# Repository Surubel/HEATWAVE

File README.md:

View this project on [CADLAB.io](https://cadlab.io/project/23592). 

# HEATWAVE
An experiment into flight controllers for racing drones.

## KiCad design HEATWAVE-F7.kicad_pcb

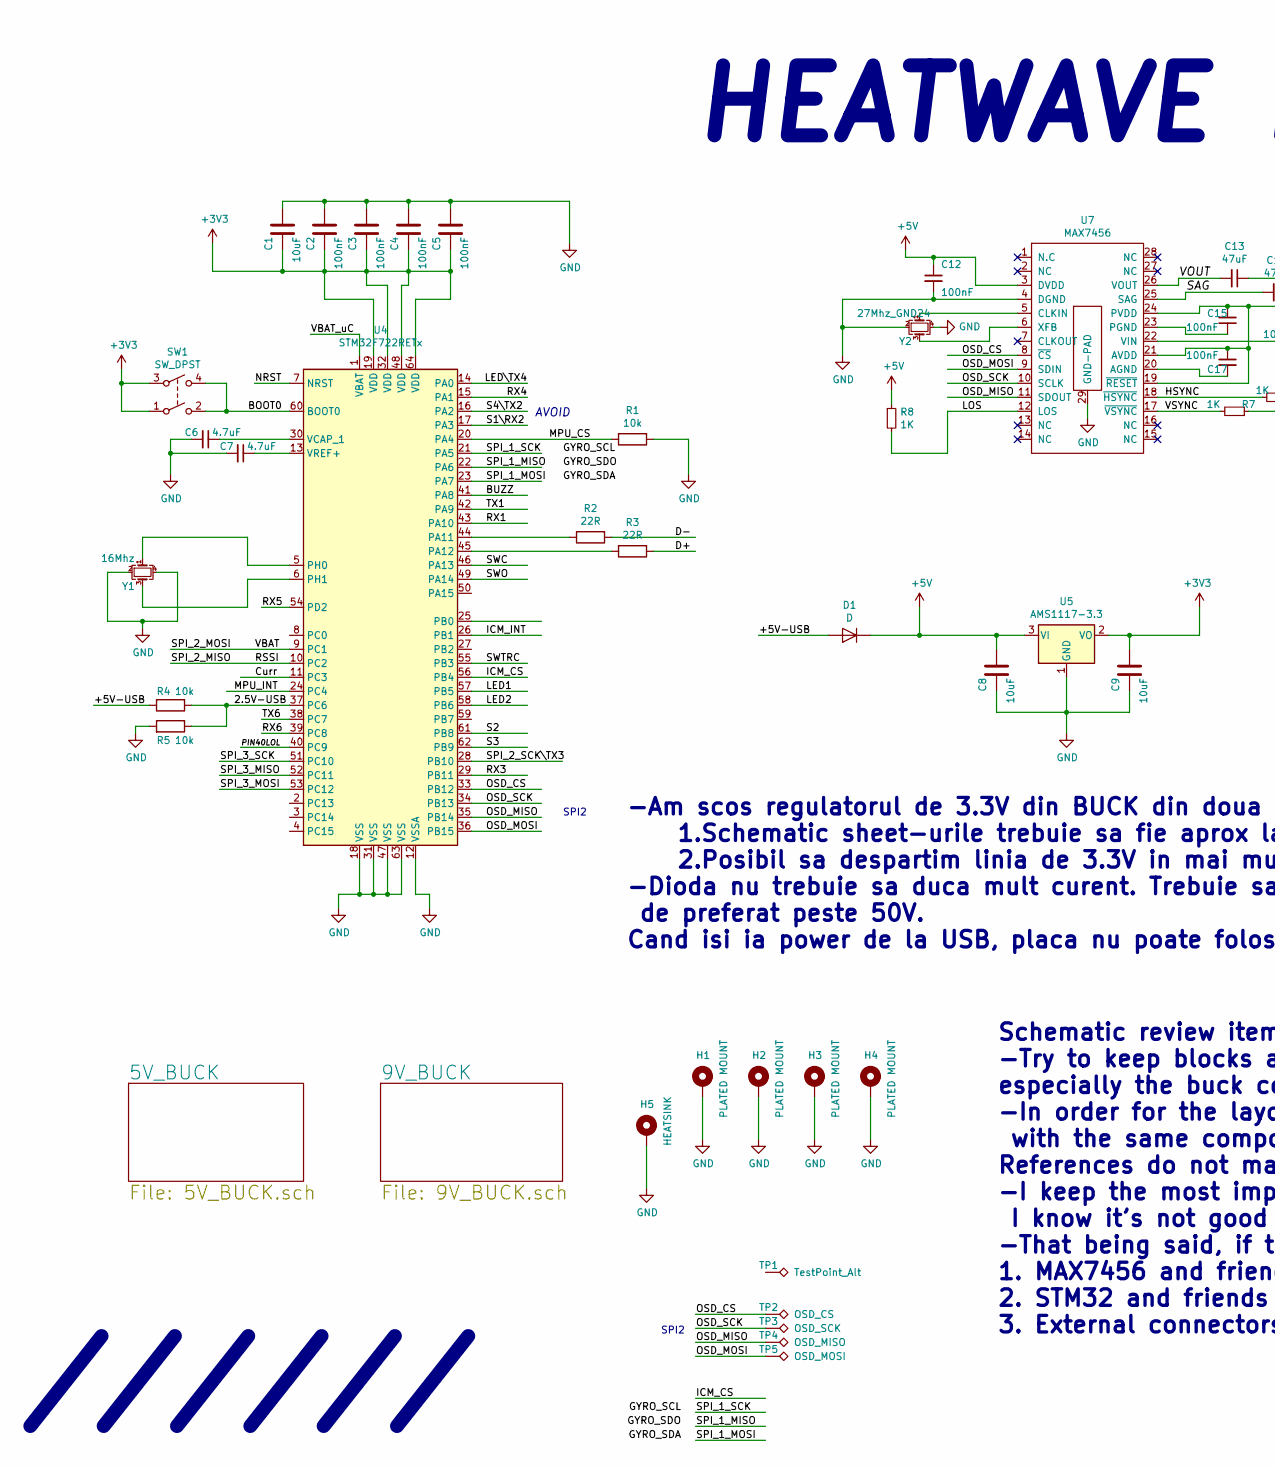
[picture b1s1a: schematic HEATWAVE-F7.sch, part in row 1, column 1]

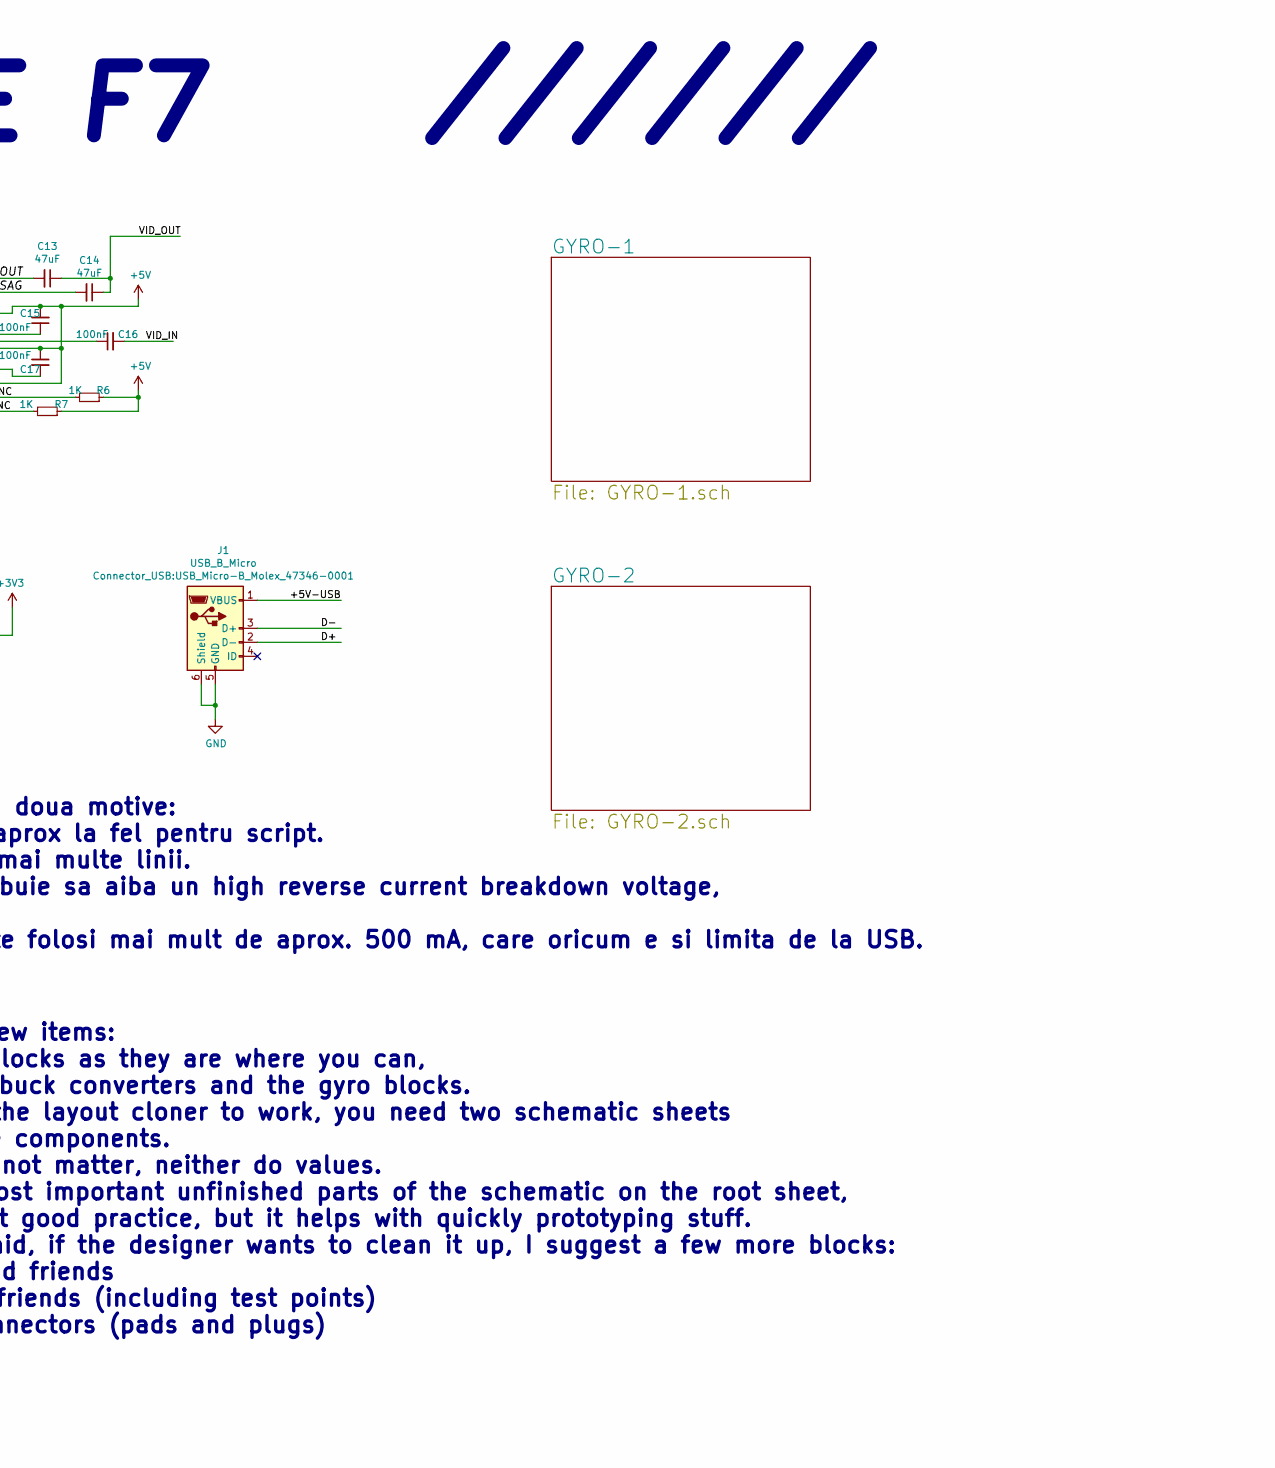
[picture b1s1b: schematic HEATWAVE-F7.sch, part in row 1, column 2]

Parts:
C1, C8, C9: 10uF; C_0805_2012Metric
C2, C3, C4, C5, C12, C15, C16, C17: 100nF; C_0805_2012Metric
C6, C7: 4.7uF; C_0402_1005Metric
C13, C14: 47uF; C_1210_3225Metric
D1: D; D_0805_2012Metric
H1, H2, H3, H4: PLATED MOUNT; MountingHole_4.5mm_Pad_Via
H5: HEATSINK; Heatsink_Aavid-TV5G_TO220_Horizontal
J1: USB_B_Micro; USB_Micro-B_Molex_47346-0001
R1, R4, R5: 10k; R_0402_1005Metric
R2, R3: 22R; R_0402_1005Metric
R6, R7, R8: 1K; R_0402_1005Metric
SW1: SW_DPST; SW_SPST_SKQG_WithoutStem
TP1: TestPoint_Alt
TP2: OSD_CS
TP3: OSD_SCK
TP4: OSD_MISO
TP5: OSD_MOSI
U4: STM32F722RETx; LQFP-64_10x10mm_P0.5mm
U5: AMS1117-3.3; SOT-223-3_TabPin2
U7: MAX7456; TSSOP-28-1EP_4.4x9.7mm_P0.65mm
Y1: 16Mhz; Resonator_SMD_muRata_CSTxExxV-3Pin_3.0x1.1mm
Y2: 27Mhz_GND24; Resonator_SMD_muRata_CSTxExxV-3Pin_3.0x1.1mm

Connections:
+3V3: C1.1, C2.1, C3.1, C4.1, C5.1, C9.2, SW1.1, SW1.3, U4.19 (VDD), U4.32 (VDD), U4.48 (VDD), U4.64 (VDD), U5.2 (VO); also elsewhere on the board
+5V: C8.2, C12.1, C15.2, C17.1, D1.1 (K), R6.1, R7.1, R8.1, U5.3 (VI), U7.3 (DVDD), U7.19 (~RESET), U7.21 (AVDD), U7.24 (PVDD); also elsewhere on the board
/2.5V-USB: R4.1, R5.1, U4.37 (PC6)
/+5V-USB: D1.2 (A), J1.1 (VBUS), R4.2
/BOOT0: SW1.2, SW1.4, U4.60 (BOOT0)
/BUZZ: U4.41 (PA8)
/Curr: U4.11 (PC3)
/D+: J1.2 (D-), R3.1
/D-: J1.3 (D+), R2.1
/HSYNC: R6.2, U7.18 (~HSYNC)
/ICM_CS: U4.56 (PB4)
/ICM_INT: U4.26 (PB1)
/LED1: U4.57 (PB5)
/LED2: U4.58 (PB6)
/LED\TX4: U4.14 (PA0)
/LOS: R8.2, U7.12 (LOS)
/MPU_CS: R1.2, U4.20 (PA4)
/MPU_INT: U4.24 (PC4)
/NRST: U4.7 (NRST)
/OSD_CS: TP2.1, U4.33 (PB12), U7.8 (~CS)
/OSD_MISO: TP4.1, U4.35 (PB14), U7.11 (SDOUT)
/OSD_MOSI: TP5.1, U4.36 (PB15), U7.9 (SDIN)
/OSD_SCK: TP3.1, U4.34 (PB13), U7.10 (SCLK)
/PIN40LOL: U4.40 (PC9)
/RSSI: U4.10 (PC2)
/RX1: U4.43 (PA10)
/RX3: U4.29 (PB11)
/RX4: U4.15 (PA1)
/RX5: U4.54 (PD2)
/RX6: U4.39 (PC8)
/S1\RX2: U4.17 (PA3)
/S2: U4.61 (PB8)
/S3: U4.62 (PB9)
/S4\TX2: U4.16 (PA2)
/SAG: C14.2, U7.25 (SAG)
/SPI_1_MISO: U4.22 (PA6)
/SPI_1_MOSI: U4.23 (PA7)
/SPI_1_SCK: U4.21 (PA5)
/SPI_2_MOSI: U4.9 (PC1)
/SPI_2_SCK\TX3: U4.28 (PB10)
/SPI_3_MISO: U4.52 (PC11)
/SPI_3_MOSI: U4.53 (PC12)
/SPI_3_SCK: U4.51 (PC10)
/SWC: U4.46 (PA13)
/SWO: U4.49 (PA14)
/SWTRC: U4.55 (PB3)
/TX1: U4.42 (PA9)
/TX6: U4.38 (PC7)
/VBAT_uC: U4.1 (VBAT)
/VID_IN: C16.2
/VID_OUT: C13.1, C14.1
/VOUT: C13.2, U7.26 (VOUT)
/VSYNC: R7.2, U7.17 (~VSYNC)
GND: C1.2, C2.2, C3.2, C4.2, C5.2, C6.2, C7.2, C8.1, C9.1, C12.2, H1.1, H2.1, H3.1, H4.1, H5.1, J1.5 (GND), J1.6 (Shield), R1.1, R5.2, U4.12 (VSSA), U4.18 (VSS), U4.31 (VSS), U4.47 (VSS), U4.63 (VSS), U5.1 (GND), U7.4 (DGND), U7.29 (GND-PAD), Y1.2, Y1.4, Y2.2, Y2.4; also elsewhere on the board
unnamed: C6.1, U4.30 (VCAP_1)
unnamed: C7.1, U4.13 (VREF+)
unnamed: C15.1, U7.23 (PGND)
unnamed: C16.1, U7.22 (VIN)
unnamed: C17.2, U7.20 (AGND)
unnamed: R2.2, U4.44 (PA11)
unnamed: R3.2, U4.45 (PA12)
unnamed: U4.5 (PH0), Y1.1
unnamed: U4.6 (PH1), Y1.3
unnamed: U7.5 (CLKIN), Y2.1
unnamed: U7.6 (XFB), Y2.3

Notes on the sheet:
HEATWAVE F7
//////
AVOID
SPI2
-Am scos regulatorul de 3.3V din BUCK din doua motive: 1.Schematic sheet-urile trebuie sa fie aprox la fel pentru script. 2.Posibil sa despartim linia de 3.3V in mai multe linii. -Dioda nu trebuie sa duca mult curent. Trebuie sa aiba un high reverse current breakdown voltage, de preferat peste 50V.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
Schematic review items: -Try to keep blocks as they are where you can, especially the buck converters and the gyro blocks. -In order for the layout cloner to work, you need two schematic sheets with the same components. References do not matter, neither do values. -I keep the most important unfinis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

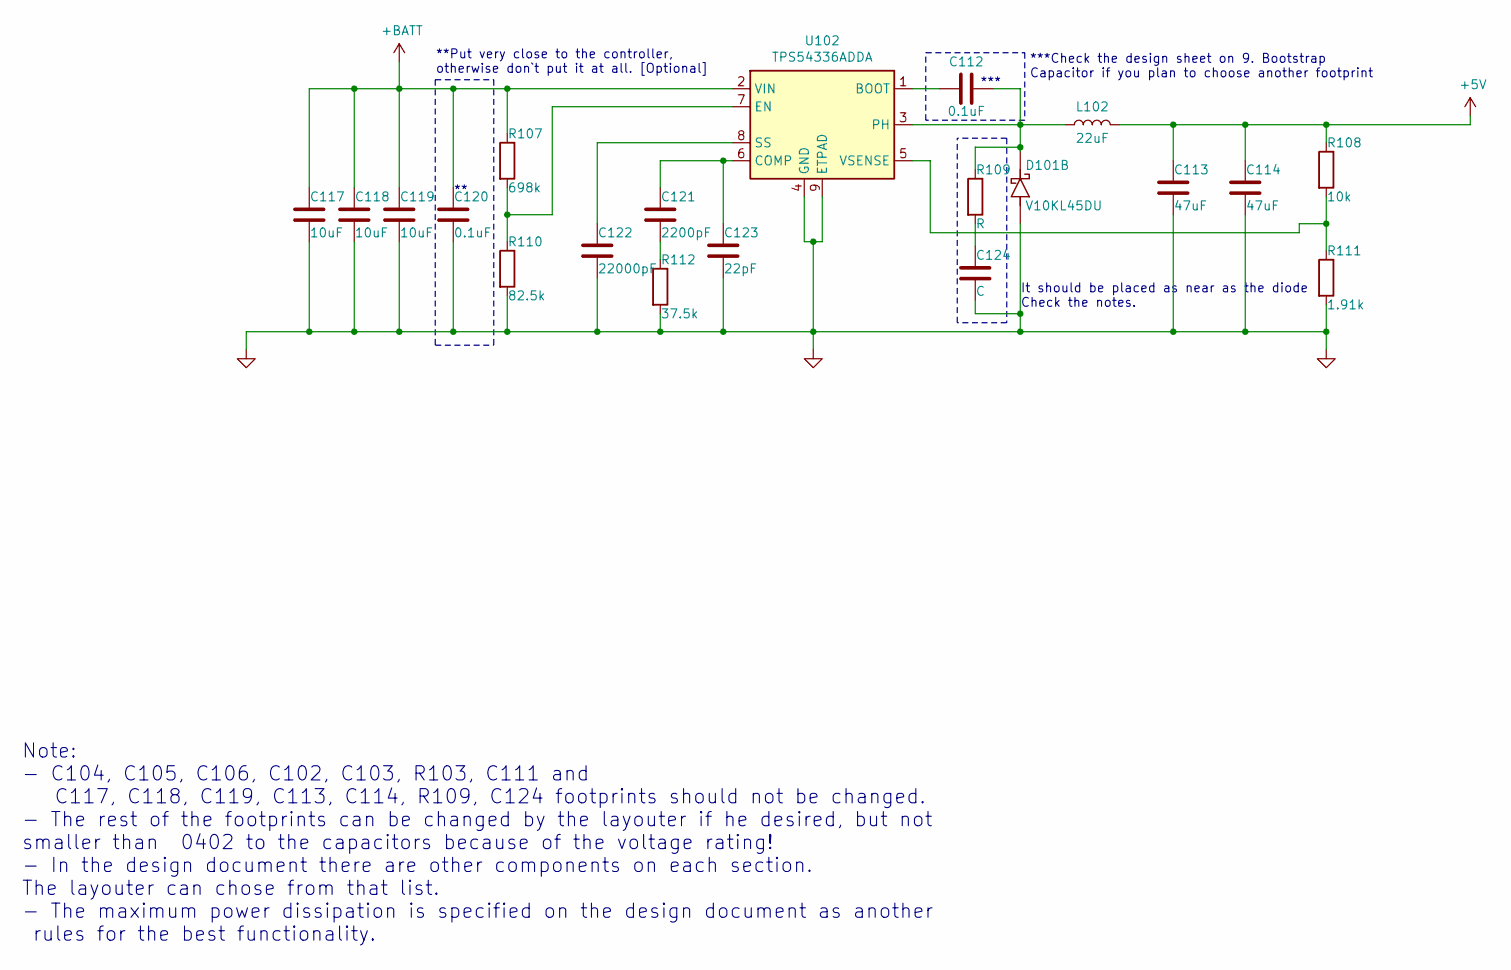
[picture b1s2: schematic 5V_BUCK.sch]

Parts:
C112, C120: 0.1uF; C_0805_2012Metric
C113, C114: 47uF; C_1210_3225Metric
C117, C118, C119: 10uF; C_1206_3216Metric
C121: 2200pF; C_0805_2012Metric
C122: 22000pF; C_0805_2012Metric
C123: 22pF; C_0805_2012Metric
C124: C; C_0805_2012Metric
D101: V10KL45DU; FlatPAK
L102: 22uF; L_Panasonic_PCC-M0748M_7.4x7mm
R107: 698k; R_0402_1005Metric
R108: 10k; R_0402_1005Metric
R109: R; R_0805_2012Metric
R110: 82.5k; R_0402_1005Metric
R111: 1.91k; R_0402_1005Metric
R112: 37.5k; R_0402_1005Metric
U102: TPS54336ADDA; TI_SO-PowerPAD-8_ThermalVias

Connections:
+5V: C113.1, C114.1, L102.2, R108.1; also elsewhere on the board
+BATT: C117.1, C118.1, C119.1, C120.1, R107.1, U102.2 (VIN); also elsewhere on the board
GND: C113.2, C114.2, C117.2, C118.2, C119.2, C120.2, C122.2, C123.2, C124.2, D101.1 (A), D101.2 (K), R110.2, R111.2, R112.2, U102.4 (GND), U102.9 (ETPAD); also elsewhere on the board
unnamed: C112.1, D101.7 (K), D101.8 (K), D101.F2 (A), L102.1, R109.1, U102.3 (PH)
unnamed: C112.2, U102.1 (BOOT)
unnamed: C121.1, C123.1, U102.6 (COMP)
unnamed: C121.2, R112.1
unnamed: C122.1, U102.8 (SS)
unnamed: C124.1, R109.2
unnamed: R107.2, R110.1, U102.7 (EN)
unnamed: R108.2, R111.1, U102.5 (VSENSE)

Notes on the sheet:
**Put very close to the controller, otherwise don`t put it at all. [Optional]
Note: - C104, C105, C106, C102, C103, R103, C111 and C117, C118, C119, C113, C114, R109, C124 footprints should not be changed. - The rest of the footprints can be changed by the layouter if he desired, but not smaller than 0402 to the capacitors because of the voltage rating! - In the design docum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
***
***Check the design sheet on 9. Bootstrap Capacitor if you plan to choose another footprint
It should be placed as near as the diode Check the notes.

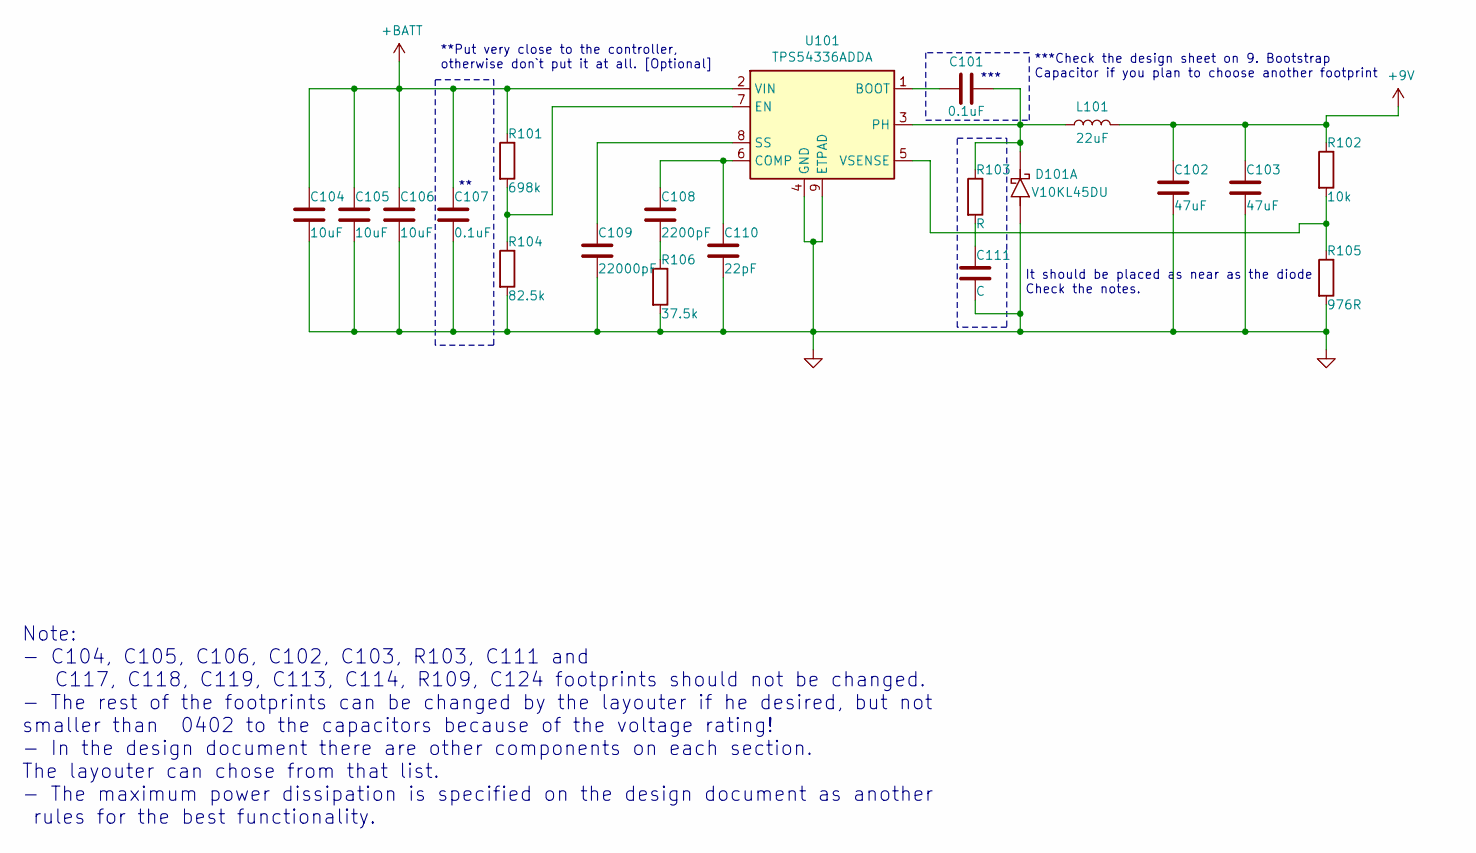
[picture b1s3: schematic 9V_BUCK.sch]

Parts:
C101, C107: 0.1uF; C_0805_2012Metric
C102, C103: 47uF; C_1210_3225Metric
C104, C105, C106: 10uF; C_1206_3216Metric
C108: 2200pF; C_0805_2012Metric
C109: 22000pF; C_0805_2012Metric
C110: 22pF; C_0805_2012Metric
C111: C; C_0805_2012Metric
D101: V10KL45DU; FlatPAK
L101: 22uF; L_Panasonic_PCC-M0748M_7.4x7mm
R101: 698k; R_0402_1005Metric
R102: 10k; R_0402_1005Metric
R103: R; R_0805_2012Metric
R104: 82.5k; R_0402_1005Metric
R105: 976R; R_0402_1005Metric
R106: 37.5k; R_0402_1005Metric
U101: TPS54336ADDA; TI_SO-PowerPAD-8_ThermalVias

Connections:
+9V: C102.1, C103.1, L101.2, R102.1
+BATT: C104.1, C105.1, C106.1, C107.1, R101.1, U101.2 (VIN); also elsewhere on the board
GND: C102.2, C103.2, C104.2, C105.2, C106.2, C107.2, C109.2, C110.2, C111.2, D101.3 (A), D101.4 (A), R104.2, R105.2, R106.2, U101.4 (GND), U101.9 (ETPAD); also elsewhere on the board
unnamed: C101.1, D101.5 (K), D101.6 (K), D101.F1 (K), L101.1, R103.1, U101.3 (PH)
unnamed: C101.2, U101.1 (BOOT)
unnamed: C108.1, C110.1, U101.6 (COMP)
unnamed: C108.2, R106.1
unnamed: C109.1, U101.8 (SS)
unnamed: C111.1, R103.2
unnamed: R101.2, R104.1, U101.7 (EN)
unnamed: R102.2, R105.1, U101.5 (VSENSE)

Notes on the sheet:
**Put very close to the controller, otherwise don`t put it at all. [Optional]
Note: - C104, C105, C106, C102, C103, R103, C111 and C117, C118, C119, C113, C114, R109, C124 footprints should not be changed. - The rest of the footprints can be changed by the layouter if he desired, but not smaller than 0402 to the capacitors because of the voltage rating! - In the design docum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
***Check the design sheet on 9. Bootstrap Capacitor if you plan to choose another footprint
***
It should be placed as near as the diode Check the notes.

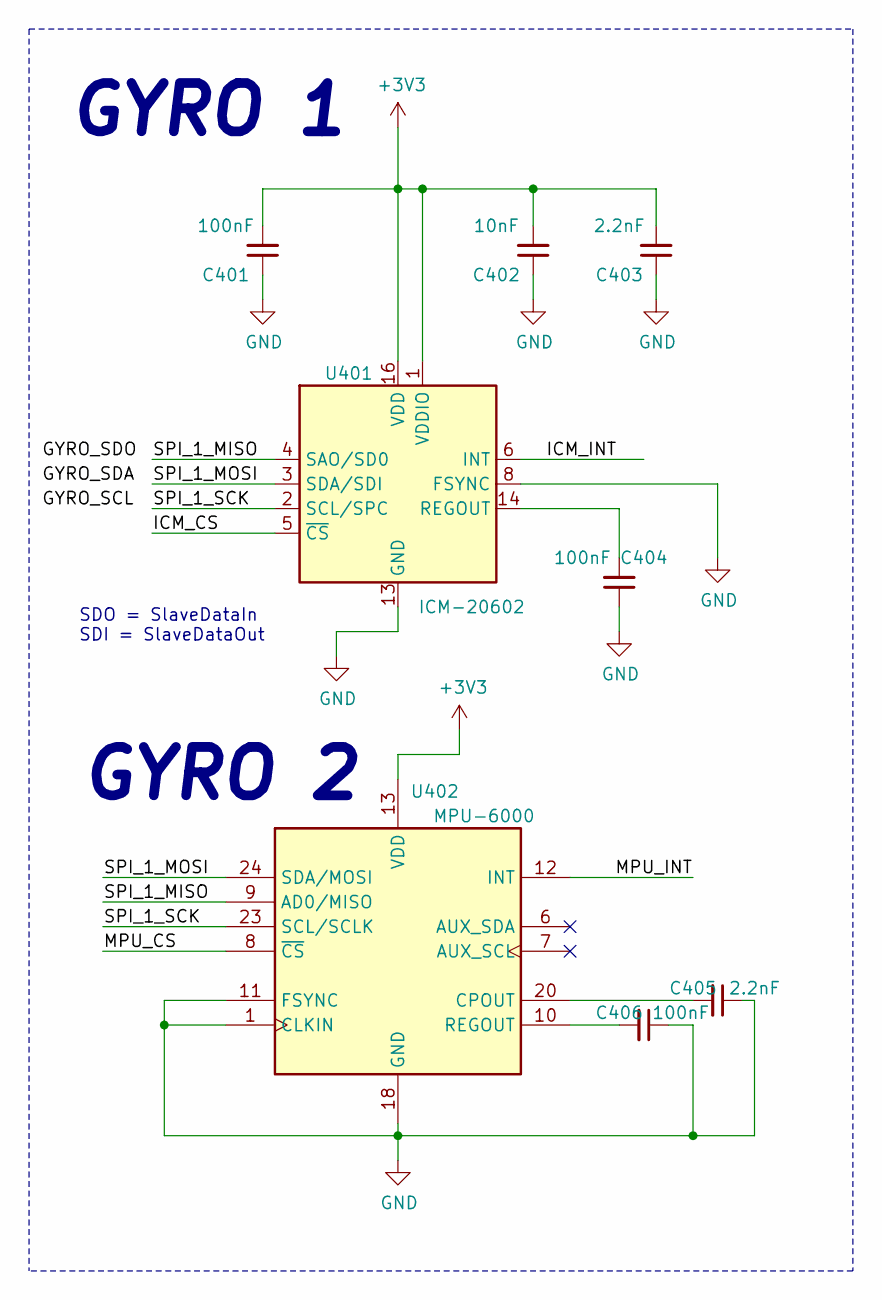
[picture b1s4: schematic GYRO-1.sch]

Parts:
C401, C404: 100nF; C_0805_2012Metric
C402: 10nF; C_0402_1005Metric
C403, C405: 2.2nF; C_0402_1005Metric
C406: 100nF; C_0402_1005Metric
U401: ICM-20602; LGA-16_3x3mm_P0.5mm_LayoutBorder3x5y
U402: MPU-6000; InvenSense_QFN-24_4x4mm_P0.5mm

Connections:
+3V3: C401.2, C402.2, C403.2, U401.1 (VDDIO), U401.16 (VDD), U402.13 (VDD); also elsewhere on the board
/GYRO-1/ICM_CS: U401.5 (~CS)
/GYRO-1/ICM_INT: U401.6 (INT)
/GYRO-1/MPU_CS: U402.8 (~CS)
/GYRO-1/MPU_INT: U402.12 (INT)
/GYRO-1/SPI_1_MISO: U401.4 (SAO/SD0), U402.9 (AD0/MISO)
/GYRO-1/SPI_1_MOSI: U401.3 (SDA/SDI), U402.24 (SDA/MOSI)
/GYRO-1/SPI_1_SCK: U401.2 (SCL/SPC), U402.23 (SCL/SCLK)
GND: C401.1, C402.1, C403.1, C404.1, C405.1, C406.1, U401.8 (FSYNC), U401.9 (GND), U401.10 (GND), U401.11 (GND), U401.12 (GND), U401.13 (GND), U401.15 (GND), U402.1 (CLKIN), U402.11 (FSYNC), U402.18 (GND); also elsewhere on the board
unnamed: C404.2, U401.14 (REGOUT)
unnamed: C405.2, U402.20 (CPOUT)
unnamed: C406.2, U402.10 (REGOUT)

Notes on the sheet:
SDO = SlaveDataIn SDI = SlaveDataOut
GYRO 2
GYRO 1

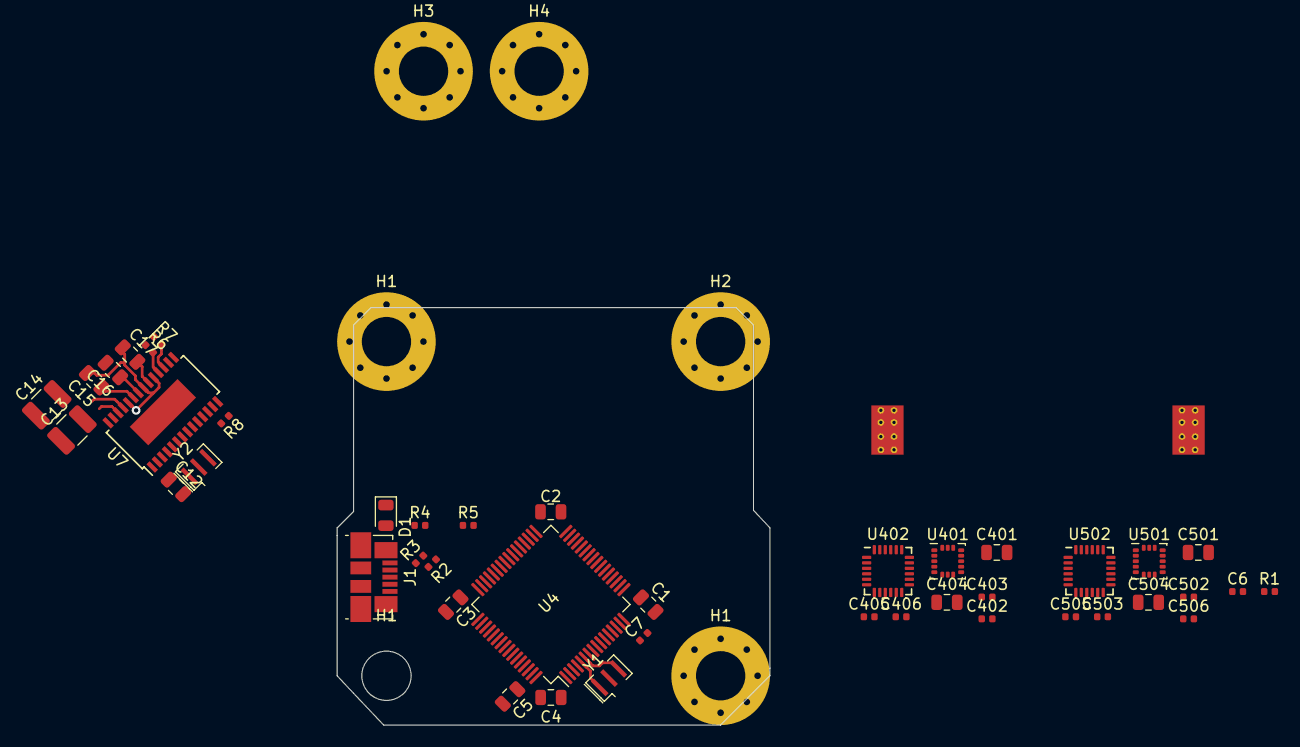
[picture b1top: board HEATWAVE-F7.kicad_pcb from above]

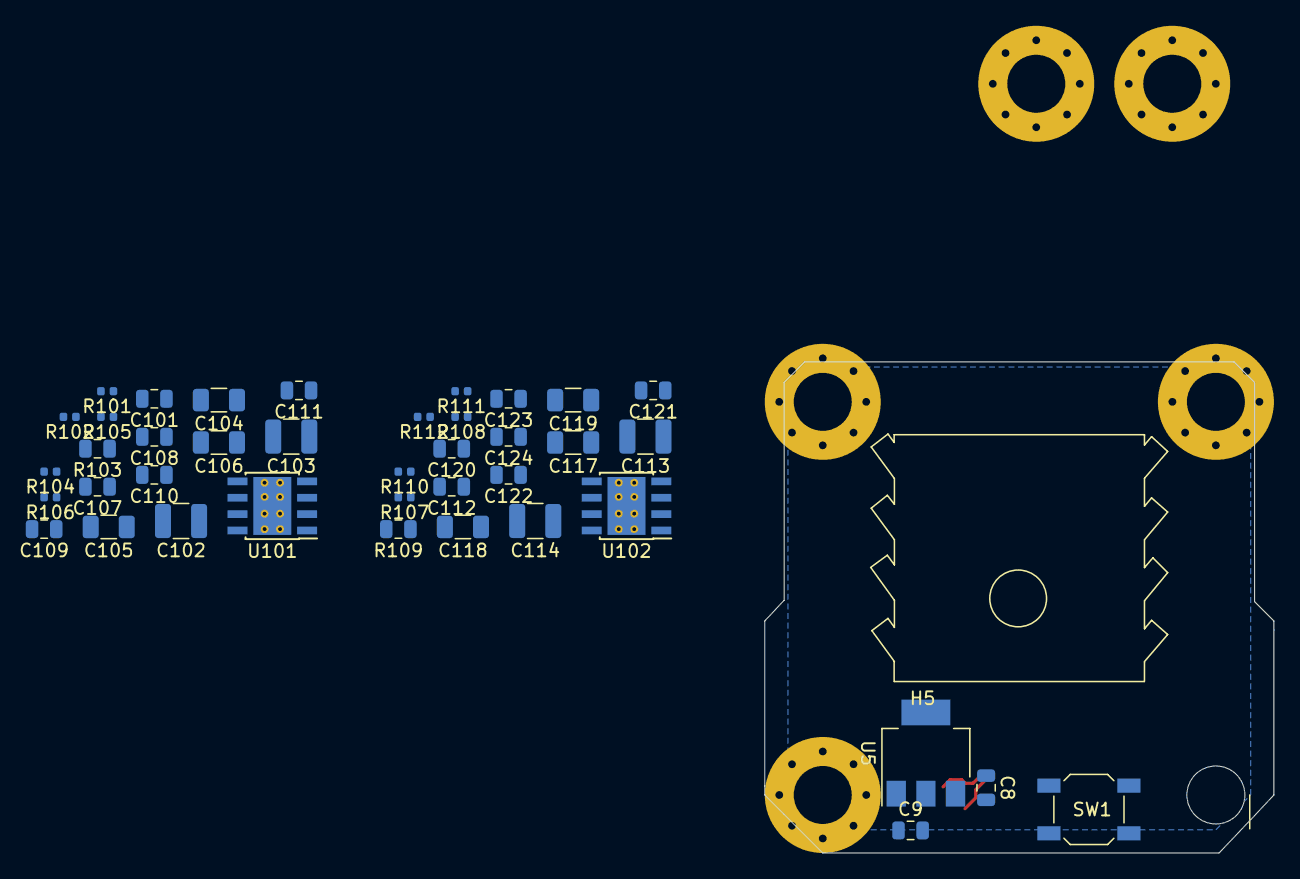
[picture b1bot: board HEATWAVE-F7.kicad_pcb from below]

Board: 2 copper layers, 39.5 x 38.1 mm, 90 parts (41 on the bottom side), 60 nets.

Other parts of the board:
C501, C504: 100nF; C_0805_2012Metric
C502: 10nF; C_0402_1005Metric
C503, C505: 2.2nF; C_0402_1005Metric
C506: 100nF; C_0402_1005Metric
H1#2, H1#3: PLATED MOUNT; MountingHole_4.5mm_Pad_Via
U501: ICM-20602; LGA-16_3x3mm_P0.5mm_LayoutBorder3x5y
U502: MPU-6000; InvenSense_QFN-24_4x4mm_P0.5mm

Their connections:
+3V3: C501.2, C502.2, C503.2, U501.1, U501.16, U502.13; also elsewhere on the board
/GYRO-2/SPI_1_MISO: U501.4, U502.9
/GYRO-2/SPI_1_MOSI: U501.3, U502.24
/GYRO-2/SPI_1_SCK: U501.2, U502.23
GND: C501.1, C502.1, C503.1, C504.1, C505.1, C506.1, H1#2.1, H1#3.1, U501.8, U501.9, U501.10, U501.11, U501.12, U501.13, U501.15, U502.1, U502.11, U502.18; also elsewhere on the board
unnamed: C504.2, U501.14
unnamed: C505.2, U502.20
unnamed: C506.2, U502.10

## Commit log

2020-11-28 FIRST COMM!!!!!!111!!!1
    I upload this for everyone who is interested in the development of open-source flight controllers.
2020-12-01 Backlink to CADLAB.io has been added.
